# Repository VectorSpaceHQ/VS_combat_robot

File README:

This is an RC controller designed for use in combat robotics. It includes PCB designs for the transmitter and receiver, as well as the necessary Arduino code. It's inspired by the work of Team Panic (https://www.instructables.com/id/Cheap-Arduino-Combat-Robot-Control/), and developed after building and using 12 of their PCBs.

Below are the changes
* Added on/off switch
* Two joysticks, as one is difficult to mix and control. They're also extremely cheap.
* Joysticks connect to female headers rather than being soldered directly. Easily replacable and easier to install.
* Uses a 3.3V Arduino Pro Mini instead of 5V
* Voltage regulator goes directly to VCC and VCC ties to NRF24. This allows powering both components through the USB programmer, no longer requiring a battery to be plugged in for testing.
* Added an LED for active communications indication
* Weapon is now an on/off switch

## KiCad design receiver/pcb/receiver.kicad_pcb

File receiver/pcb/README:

ESP32C3 pin limitations:
https://wiki.seeedstudio.com/exp32c3_d9_d6_d8/

Use D9 only as input. This is the boot button.
Use D6 only as output but it will sometimes be HIGH, so don't use it for any motors!

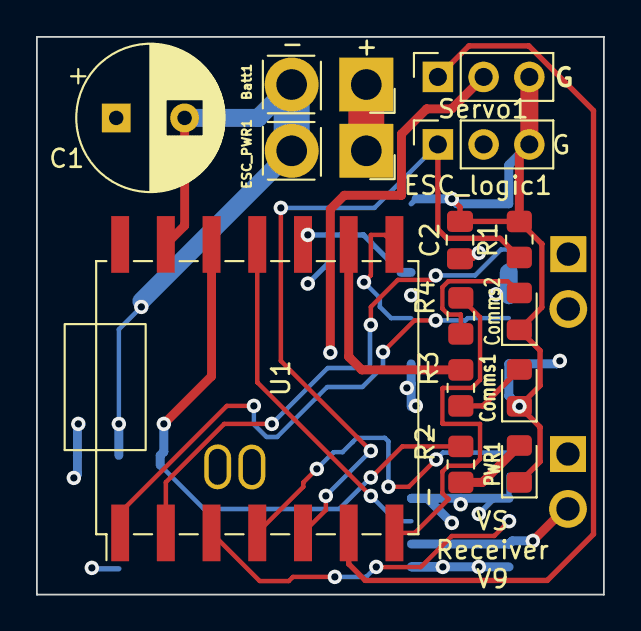
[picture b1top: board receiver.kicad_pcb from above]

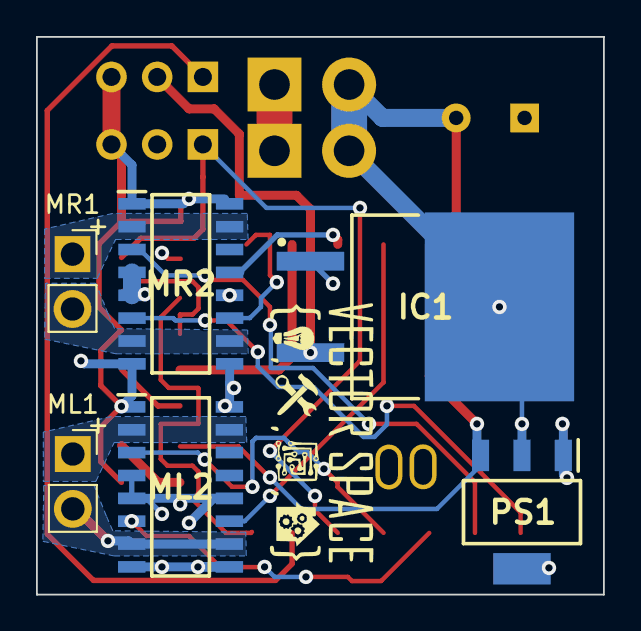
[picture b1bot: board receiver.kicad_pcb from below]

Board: 4 copper layers, 31.5 x 31.0 mm, 20 parts (6 on the bottom side), 22 nets.

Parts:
Batt1: Conn_01x02_Female; battery_pads
C1: 270 uF; CP_Radial_D8.0mm_P3.80mm
C2: 100nF; C_0805_2012Metric_Pad1.18x1.45mm_HandSolder
Comms1, Comms2: LED; LED_0805_2012Metric_Pad1.15x1.40mm_HandSolder
ESC_PWR1: Conn_01x02_Female; battery_pads
ESC_logic1: ESC; PinSocket_1x03_P2.54mm_Vertical
IC1: L7806CD2T-TR; TO254P1542X460-3N
ML1: Conn_01x02_Female; DC_motor_output
ML2: VNH7100BASTR; SOIC127P600X175-16N
MR1: motor_output; DC_motor_output
MR2: VNH7100BASTR; SOIC127P600X175-16N
PS1: UA78M33CDCYRG3; SOT230P700X180-4N
PWR1: LED; LED_0805_2012Metric_Pad1.15x1.40mm_HandSolder
R1: 10k; R_0805_2012Metric_Pad1.20x1.40mm_HandSolder
R2, R3, R4: 680 ohm; R_0805_2012Metric_Pad1.20x1.40mm_HandSolder
Servo1: Servo; PinSocket_1x03_P2.54mm_Vertical
U1: XIAO ESP32C3; xiao_esp32c3

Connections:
+3V3: PS1.3 (OUTPUT), R2.1, U1.12 (VCC_3V3)
+6V: IC1.3 (OUTPUT), Servo1.2
+12V: Batt1.1, C1.1, C2.1, ESC_PWR1.1, IC1.1 (INPUT), ML2.4 (VCC_1), ML2.5 (VCC_2), ML2.12 (VCC_3), MR2.4 (VCC_1), MR2.5 (VCC_2), MR2.12 (VCC_3), PS1.1 (INPUT)
/ML_PWM: ML2.11 (PWM), U1.11 (D10)
/MR_PWM: MR2.11 (PWM), U1.8 (D7)
/MR_sense: MR2.13 (CS), U1.10 (D9)
GND: Batt1.2, C1.2, C2.2, Comms1.1 (K), Comms2.1 (K), ESC_PWR1.2, ESC_logic1.3, IC1.4 (GND_(THERMALPAD)), ML2.1 (GNDA_1), ML2.8 (GNDB_1), ML2.9 (GNDB_2), ML2.16 (GNDA_2), MR2.1 (GNDA_1), MR2.8 (GNDB_1), MR2.9 (GNDB_2), MR2.16 (GNDA_2), PS1.2 (COMMON_1), PS1.4 (COMMON_2), PWR1.1 (K), R1.1, Servo1.3, U1.13 (GND)
unnamed: Comms1.2 (A), R3.2
unnamed: Comms2.2 (A), R4.2
unnamed: ESC_logic1.1, R1.2, U1.5 (D4)
unnamed: ML1.1, ML2.2 (OUTA_1), ML2.15 (OUTA_2)
unnamed: ML1.2, ML2.7 (OUTB_1), ML2.10 (OUTB_2)
unnamed: ML2.3 (INA), U1.4 (D3)
unnamed: ML2.6 (INB), U1.3 (D2)
unnamed: MR1.1, MR2.2 (OUTA_1), MR2.15 (OUTA_2)
unnamed: MR1.2, MR2.7 (OUTB_1), MR2.10 (OUTB_2)
unnamed: MR2.3 (INA), U1.2 (D1)
unnamed: MR2.6 (INB), U1.1 (D0)
unnamed: PWR1.2 (A), R2.2
unnamed: Servo1.1, U1.6 (D5)
unnamed: R4.1, U1.7 (D6)
unnamed: R3.1, U1.9 (D8)

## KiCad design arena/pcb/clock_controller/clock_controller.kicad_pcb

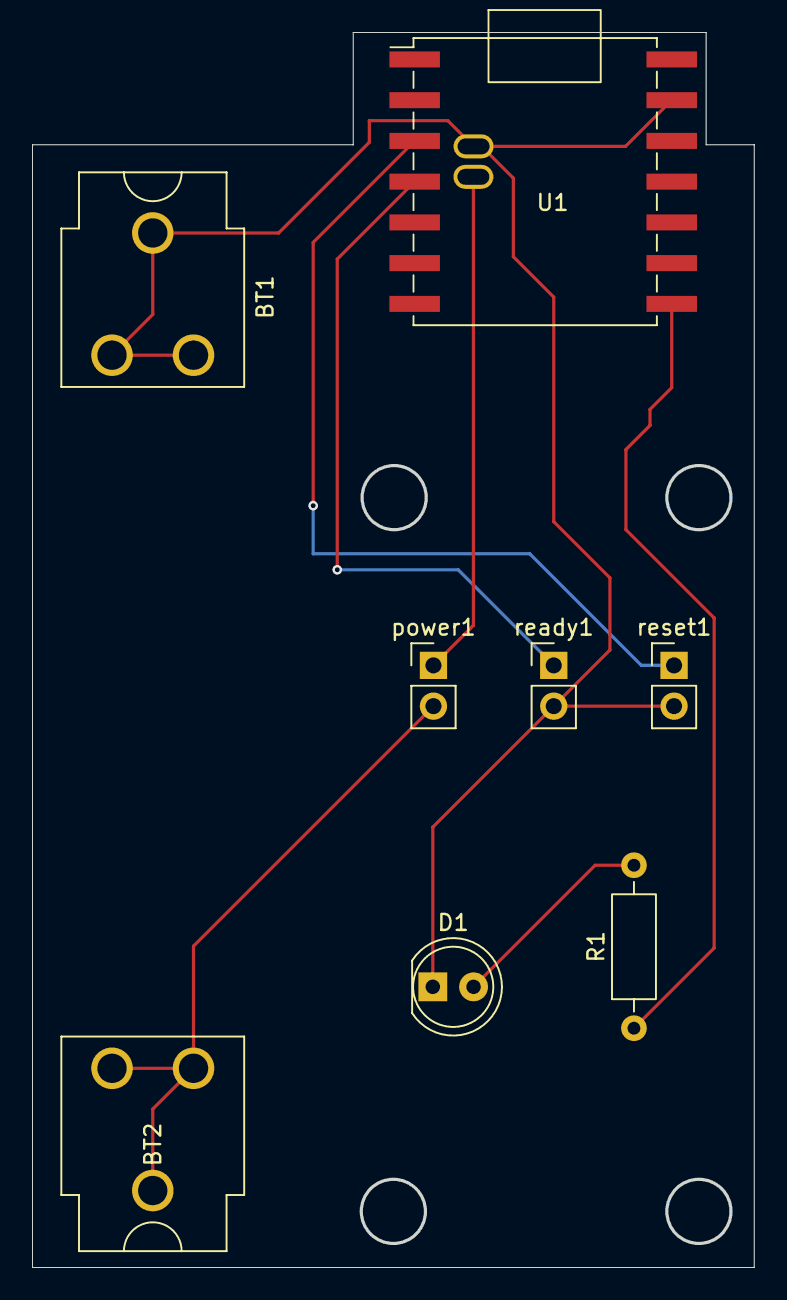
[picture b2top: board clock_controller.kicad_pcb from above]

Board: 2 copper layers, 44.9 x 76.9 mm, 8 parts (0 on the bottom side), 7 nets.

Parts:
BT1, BT2: 54; BatteryClip_Keystone_54_D16-19mm
D1: LED; LED_D5.0mm_FlatTop
R1: R_US; R_Axial_DIN0207_L6.3mm_D2.5mm_P10.16mm_Horizontal
U1: XIAO ESP32C3; xiao_esp32c3
power1: SW_SPDT; PinHeader_1x02_P2.54mm_Vertical
ready1: SW_Push; PinHeader_1x02_P2.54mm_Vertical
reset1: SW_Push; PinHeader_1x02_P2.54mm_Vertical

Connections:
+3.3V: U1.B+ (Batt+), power1.1 (A)
GND: BT1.1, D1.1 (K), U1.13 (GND), U1.B- (Batt-), ready1.2, reset1.2
unnamed: BT2.1 (A), power1.2 (B)
unnamed: D1.2 (A), R1.2
unnamed: U1.3 (D2), reset1.1
unnamed: U1.4 (D3), ready1.1
unnamed: R1.1, U1.8 (D7)

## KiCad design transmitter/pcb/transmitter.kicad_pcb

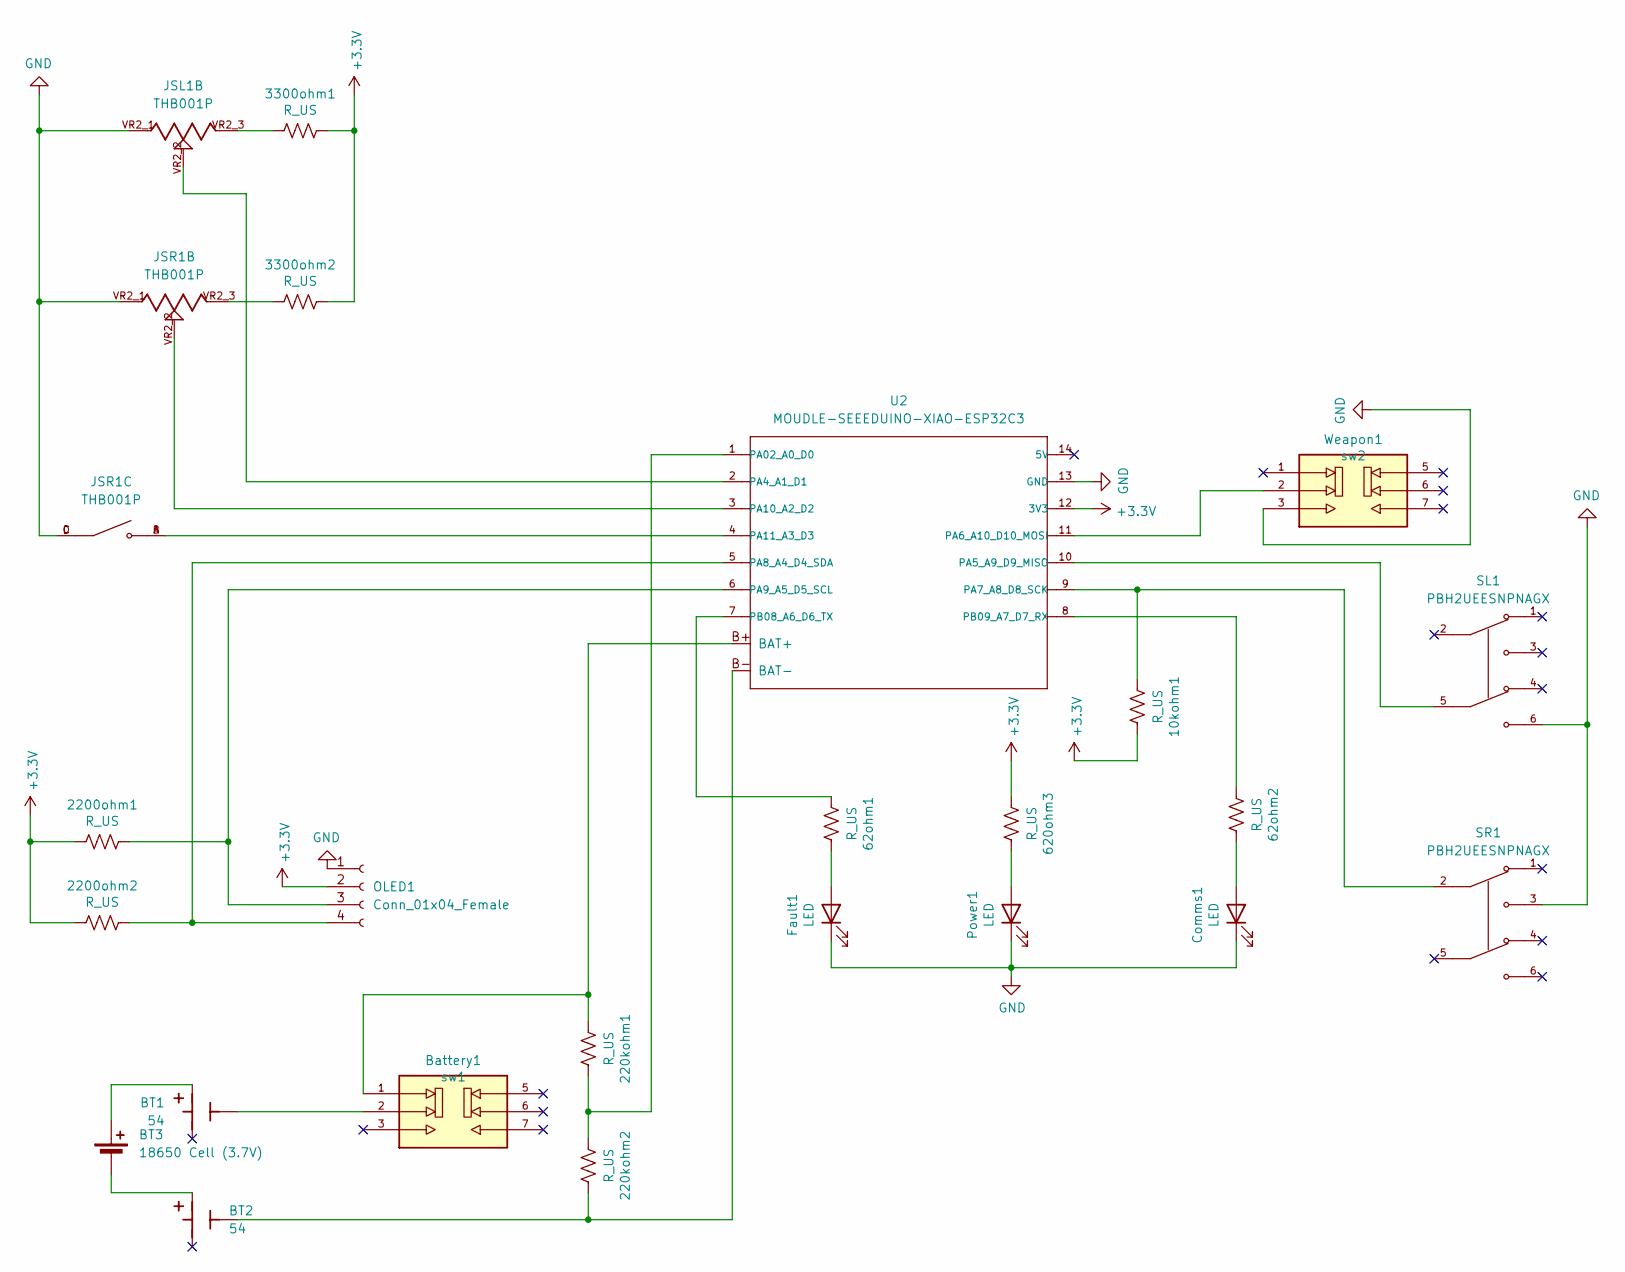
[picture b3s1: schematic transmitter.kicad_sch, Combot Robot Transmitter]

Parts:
10kohm1, 62ohm1, 62ohm2, 220kohm1, 220kohm2, 620ohm3, 2200ohm1, 2200ohm2, 3300ohm1, 3300ohm2: R_US; R_0805_2012Metric_Pad1.20x1.40mm_HandSolder
BT1, BT2: 54; BAT_54; PARTREV E
BT3: 18650 Cell (3.7V)
Battery1: sw1; SW_JS202011JCQN; PARTREV 11 Nov 19
Comms1: LED; LED_0805_2012Metric_Pad1.15x1.40mm_HandSolder
Fault1: LED; LED_0805_2012Metric_Pad1.15x1.40mm_HandSolder
JSL1: THB001P; CNK_THB001P; PARTREV 27 Jan 22
JSR1: THB001P; CNK_THB001P; PARTREV 27 Jan 22
OLED1: Conn_01x04_Female; PinSocket_1x04_P2.54mm_Vertical
Power1: LED; LED_0805_2012Metric_Pad1.15x1.40mm_HandSolder
SL1: PBH2UEESNPNAGX; SW_PBH2UEESNPNAGX; PARTREV E
SR1: PBH2UEESNPNAGX; SW_PBH2UEESNPNAGX; PARTREV E
U2: MOUDLE-SEEEDUINO-XIAO-ESP32C3; MOUDLE14P-SMD-2.54-21X17.8MM
Weapon1: sw2; SW_JS202011JCQN; PARTREV 11 Nov 19

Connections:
+3.3V: 10kohm1.1, 620ohm3.2, 2200ohm1.2, 2200ohm2.2, 3300ohm1.1, 3300ohm2.1, OLED1.2, U2.12 (3V3)
GND: Comms1.1 (K), Fault1.1 (K), JSL1.VR2_1, JSR1.C, JSR1.D, JSR1.VR2_1, OLED1.1, Power1.1 (K), SL1.6, SR1.3, U2.13 (GND), Weapon1.3
unnamed: 3300ohm1.2, JSL1.VR2_3
unnamed: 3300ohm2.2, JSR1.VR2_3
unnamed: BT1.1_3, Battery1.2
unnamed: BT1.1_1, BT3.1 (+)
unnamed: BT2.1_1, BT3.2 (-)
unnamed: 62ohm2.1, Comms1.2 (A)
unnamed: 62ohm1.1, Fault1.2 (A)
unnamed: 2200ohm1.1, OLED1.3, U2.6 (PA9_A5_D5_SCL)
unnamed: 2200ohm2.1, OLED1.4, U2.5 (PA8_A4_D4_SDA)
unnamed: 620ohm3.1, Power1.2 (A)
unnamed: 220kohm1.2, Battery1.1, U2.B+ (BAT+)
unnamed: 220kohm2.1, BT2.1_3, U2.B- (BAT-)
unnamed: 220kohm1.1, 220kohm2.2, U2.1 (PA02_A0_D0)
unnamed: JSL1.VR2_2, U2.2 (PA4_A1_D1)
unnamed: SL1.5, U2.10 (PA5_A9_D9_MISO)
unnamed: U2.11 (PA6_A10_D10_MOSI), Weapon1.2
unnamed: 10kohm1.2, SR1.2, U2.9 (PA7_A8_D8_SCK)
unnamed: JSR1.VR2_2, U2.3 (PA10_A2_D2)
unnamed: JSR1.A, JSR1.B, U2.4 (PA11_A3_D3)
unnamed: 62ohm1.2, U2.7 (PB08_A6_D6_TX)
unnamed: 62ohm2.2, U2.8 (PB09_A7_D7_RX)

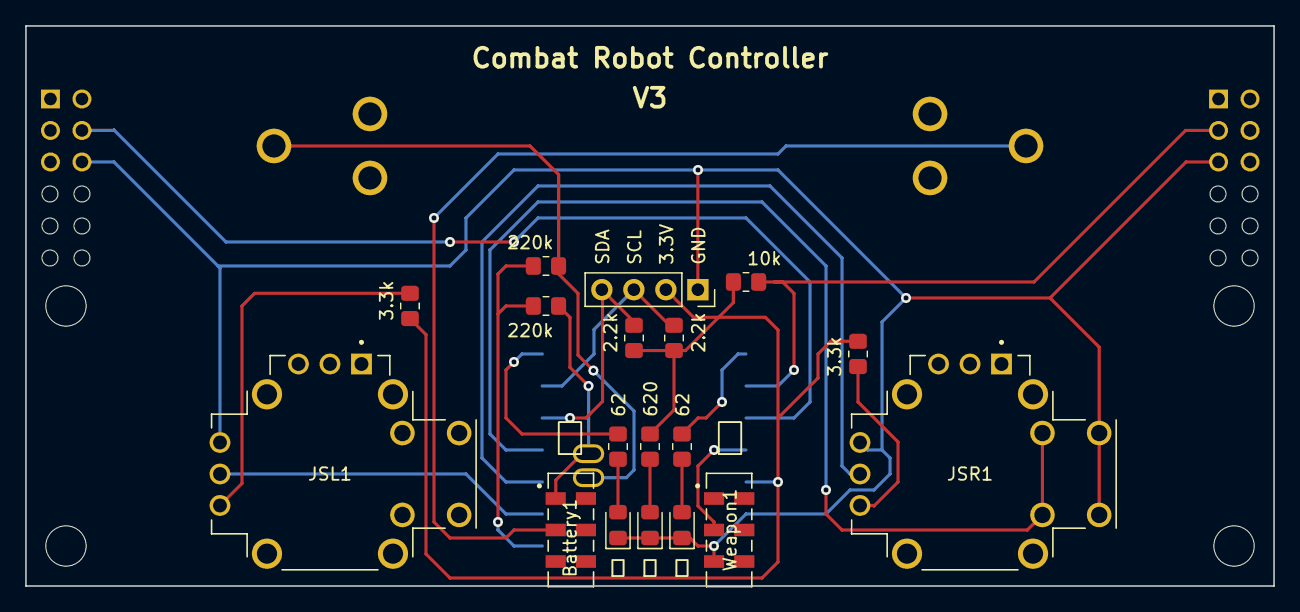
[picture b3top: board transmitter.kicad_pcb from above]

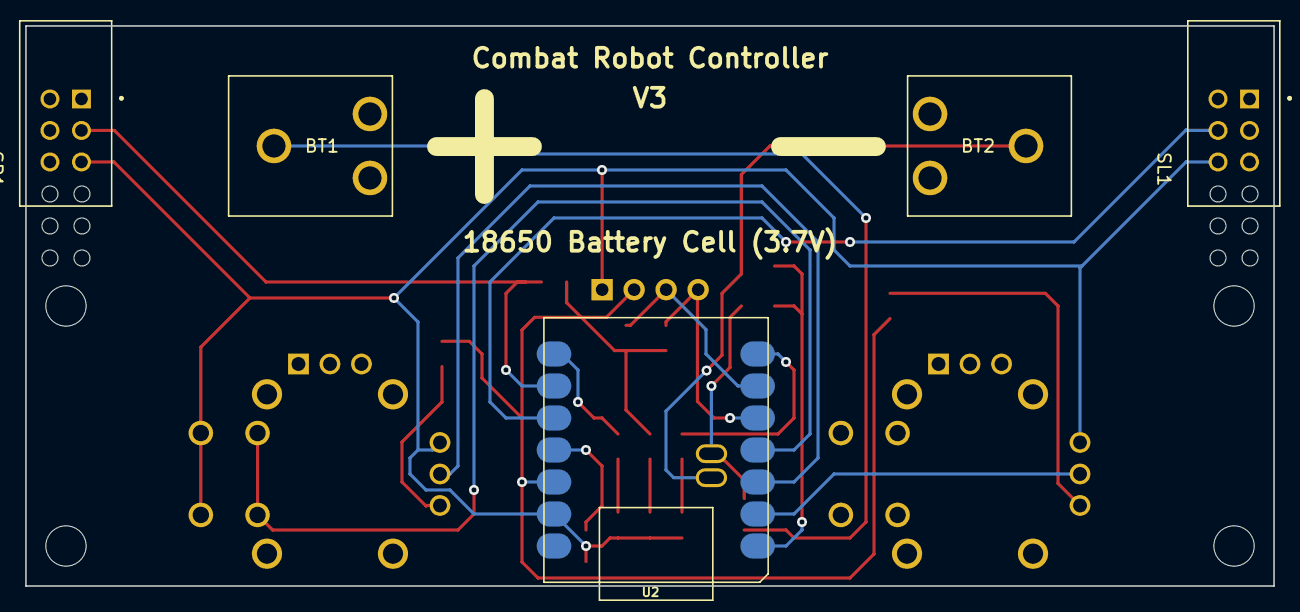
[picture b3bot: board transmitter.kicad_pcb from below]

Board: 2 copper layers, 99.1 x 44.5 mm, 23 parts (5 on the bottom side), 21 nets.

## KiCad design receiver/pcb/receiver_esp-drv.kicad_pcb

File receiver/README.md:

# Hardware
MCU: ESP32-C3
max supply voltage 3.7V

Voltage Regulator: AMS1117-3.3
Max supply voltage 15V. Regulates to 3.3V

Motor Drivers: VNH7100BASTR
Vin: 5V to 28V
15A max

# Software
## Receiver

### Compiling
1. Ensure PlatformIO Core installed
2. Click PlatformIO extension on sidebar
3. Open ./src/receiver as project.
4. Click Upload -> arrow at bottom bar.

## Transmitter
### Installation
#### Determine MAC Address of ESP32
1. Upload MAC_finder.ino using Arduino IDE
2. Look at Serial Monitor and copy down resulting MAC address
3. Copy this MAC Address into transmitter.ino

OR

Arduino IDE -> Tools -> Get Board Info

#### Determine joystick rest values

# Troubleshooting
## ESP32 Error: No serial data received

1. Open the Arduino IDE Serial Monitor
2. Hold-down the “BOOT” button
3. Press the “ENABLE” button once
4. Release the finger from the “BOOT” button

## ESP32 Error: A serial exception error occurred: Write timeout
 Press and hold the R button, then press and hold the B button, then release the R button, then release the B button.

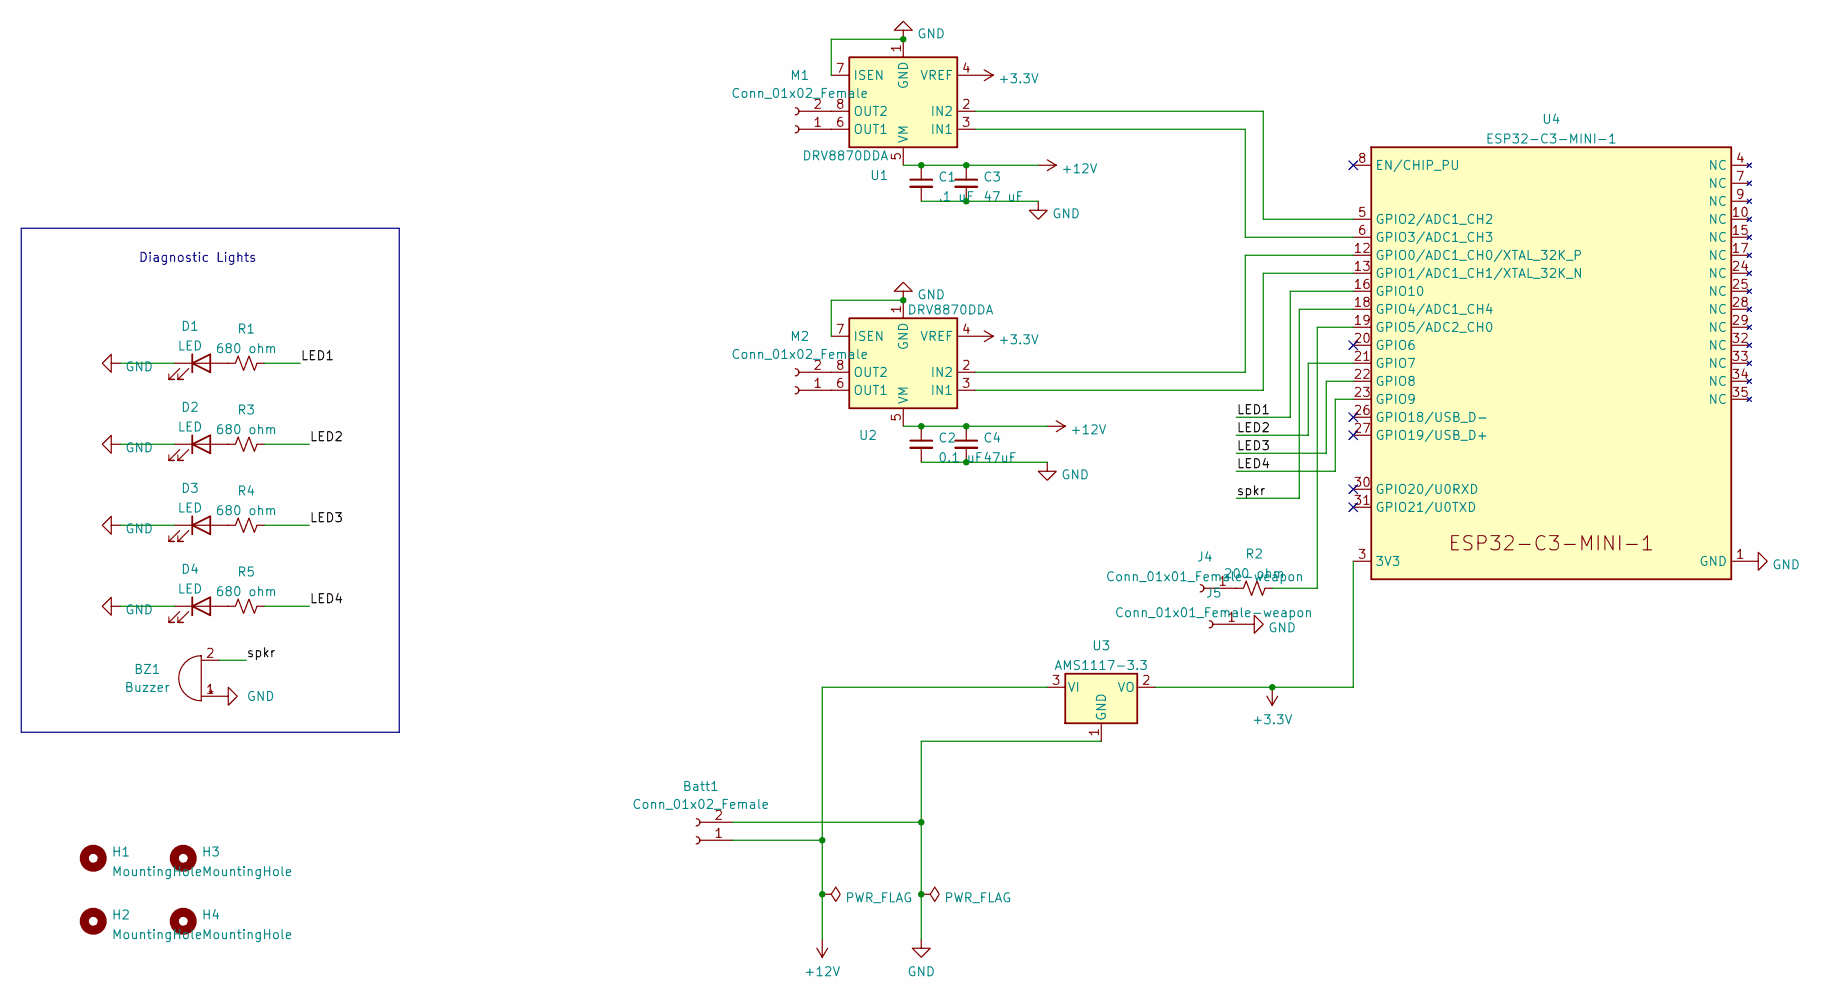
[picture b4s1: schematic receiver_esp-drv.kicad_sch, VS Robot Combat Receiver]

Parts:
BZ1: Buzzer; Buzzer_CUI_CPT-9019S-SMT
Batt1: Conn_01x02_Female; PinSocket_1x02_P2.54mm_Vertical
C1: .1 uF; C_0805_2012Metric_Pad1.18x1.45mm_HandSolder
C2: 0.1 uF; C_0805_2012Metric_Pad1.18x1.45mm_HandSolder
C3: 47 uF; C_0805_2012Metric_Pad1.18x1.45mm_HandSolder
C4: 47uF; C_0805_2012Metric_Pad1.18x1.45mm_HandSolder
D1, D2, D3, D4: LED; LED_0805_2012Metric_Pad1.15x1.40mm_HandSolder
H1, H2, H3, H4: MountingHole; MountingHole_3.2mm_M3
J4, J5: Conn_01x01_Female-weapon; PinSocket_1x01_P2.54mm_Vertical
M1, M2: Conn_01x02_Female; PinSocket_1x02_P2.54mm_Vertical
R1, R3, R4, R5: 680 ohm; R_0805_2012Metric_Pad1.20x1.40mm_HandSolder
R2: 200 ohm; R_0805_2012Metric_Pad1.20x1.40mm_HandSolder
U1, U2: DRV8870DDA; Texas_HTSOP-8-1EP_3.9x4.9mm_P1.27mm_EP2.95x4.9mm_Mask2.4x3.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
U3: AMS1117-3.3; SOT-223-3_TabPin2
U4: ESP32-C3-MINI-1; ESP32-C3

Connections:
+3V3: U1.4 (VREF), U2.4 (VREF), U3.2 (VO), U4.3 (3V3)
+12V: Batt1.1, C1.1, C2.1, C3.1, C4.1, U1.5 (VM), U2.5 (VM), U3.3 (VI)
/LED1: R1.1, U4.16 (GPIO10)
/LED2: R3.1, U4.21 (GPIO7)
/LED3: R4.1, U4.22 (GPIO8)
/LED4: R5.1, U4.23 (GPIO9)
/spkr: BZ1.2 (+), U4.18 (GPIO4/ADC1_CH4)
GND: BZ1.1 (-), Batt1.2, C1.2, C2.2, C3.2, C4.2, D1.1 (K), D2.1 (K), D3.1 (K), D4.1 (K), J5.1, U1.1 (GND), U1.7 (ISEN), U1.9 (GND), U2.1 (GND), U2.7 (ISEN), U2.9 (GND), U3.1 (GND), U4.1 (GND), U4.2 (GND), U4.36 (GND), U4.37 (GND), U4.38 (GND), U4.39 (GND), U4.40 (GND), U4.41 (GND), U4.42 (GND), U4.43 (GND), U4.44 (GND), U4.45 (GND), U4.46 (GND), U4.47 (GND), U4.48 (GND), U4.49 (GND), U4.50 (GND), U4.51 (GND), U4.52 (GND), U4.53 (GND)
unnamed: D1.2 (A), R1.2
unnamed: D2.2 (A), R3.2
unnamed: D3.2 (A), R4.2
unnamed: D4.2 (A), R5.2
unnamed: J4.1, R2.2
unnamed: M1.1, U1.6 (OUT1)
unnamed: M1.2, U1.8 (OUT2)
unnamed: M2.1, U2.6 (OUT1)
unnamed: M2.2, U2.8 (OUT2)
unnamed: R2.1, U4.19 (GPIO5/ADC2_CH0)
unnamed: U1.2 (IN2), U4.5 (GPIO2/ADC1_CH2)
unnamed: U1.3 (IN1), U4.6 (GPIO3/ADC1_CH3)
unnamed: U2.2 (IN2), U4.12 (GPIO0/ADC1_CH0/XTAL_32K_P)
unnamed: U2.3 (IN1), U4.13 (GPIO1/ADC1_CH1/XTAL_32K_N)

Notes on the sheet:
Diagnostic Lights

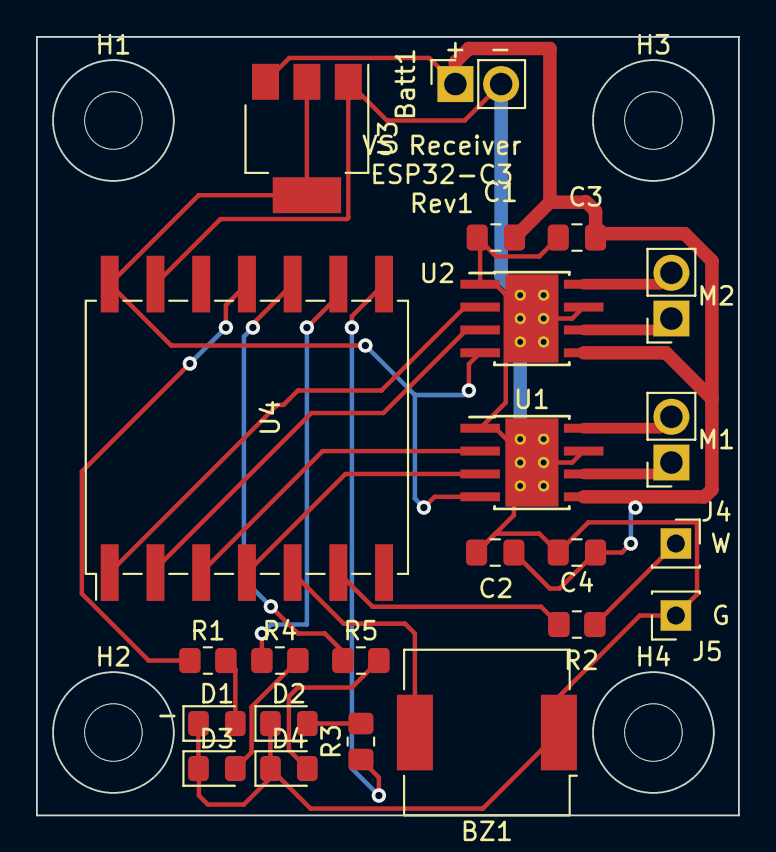
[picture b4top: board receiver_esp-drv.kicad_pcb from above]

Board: 2 copper layers, 39.0 x 43.2 mm, 27 parts (0 on the bottom side), 22 nets.

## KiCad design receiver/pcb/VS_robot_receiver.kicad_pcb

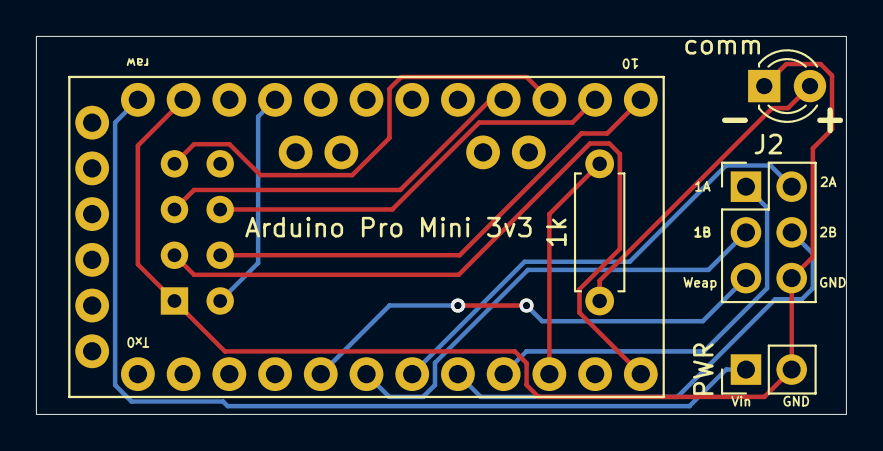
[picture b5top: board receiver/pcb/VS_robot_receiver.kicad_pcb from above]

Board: 2 copper layers, 45.0 x 21.0 mm, 6 parts (1 on the bottom side), 16 nets.

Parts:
1k: 680ohm; R_Axial_DIN0207_L6.3mm_D2.5mm_P7.62mm_Horizontal
Arduino Pro Mini 3v3: ARDUINO_PRO_MINI; MODULE_ARDUINO_PRO_MINI
J2: Conn_02x03_Odd_Even; PinHeader_2x03_P2.54mm_Vertical
NRF24: NRF24L01_Breakout; nRF24L01_Breakout
PWR: Conn_01x02_Female; PinHeader_1x02_P2.54mm_Vertical
comm: LED; LED_D3.0mm

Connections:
+3V3: Arduino Pro Mini 3v3.JP6_4, NRF24.2
+5V: Arduino Pro Mini 3v3.JP6_1, PWR.1
GND: Arduino Pro Mini 3v3.JP6_2, J2.6, NRF24.1, PWR.2, comm.1
unnamed: 1k.1, comm.2
unnamed: Arduino Pro Mini 3v3.JP7_4, J2.1
unnamed: Arduino Pro Mini 3v3.JP7_6, J2.2
unnamed: Arduino Pro Mini 3v3.JP7_7, J2.3
unnamed: Arduino Pro Mini 3v3.JP7_5, J2.4
unnamed: Arduino Pro Mini 3v3.JP7_8, J2.5
unnamed: 1k.2, Arduino Pro Mini 3v3.JP7_3
unnamed: Arduino Pro Mini 3v3.JP7_1, NRF24.3
unnamed: Arduino Pro Mini 3v3.JP6_12, NRF24.4
unnamed: Arduino Pro Mini 3v3.JP6_9, NRF24.5
unnamed: Arduino Pro Mini 3v3.JP6_11, NRF24.6
unnamed: Arduino Pro Mini 3v3.JP6_10, NRF24.7
unnamed: Arduino Pro Mini 3v3.JP1_5, Arduino Pro Mini 3v3.JP1_6

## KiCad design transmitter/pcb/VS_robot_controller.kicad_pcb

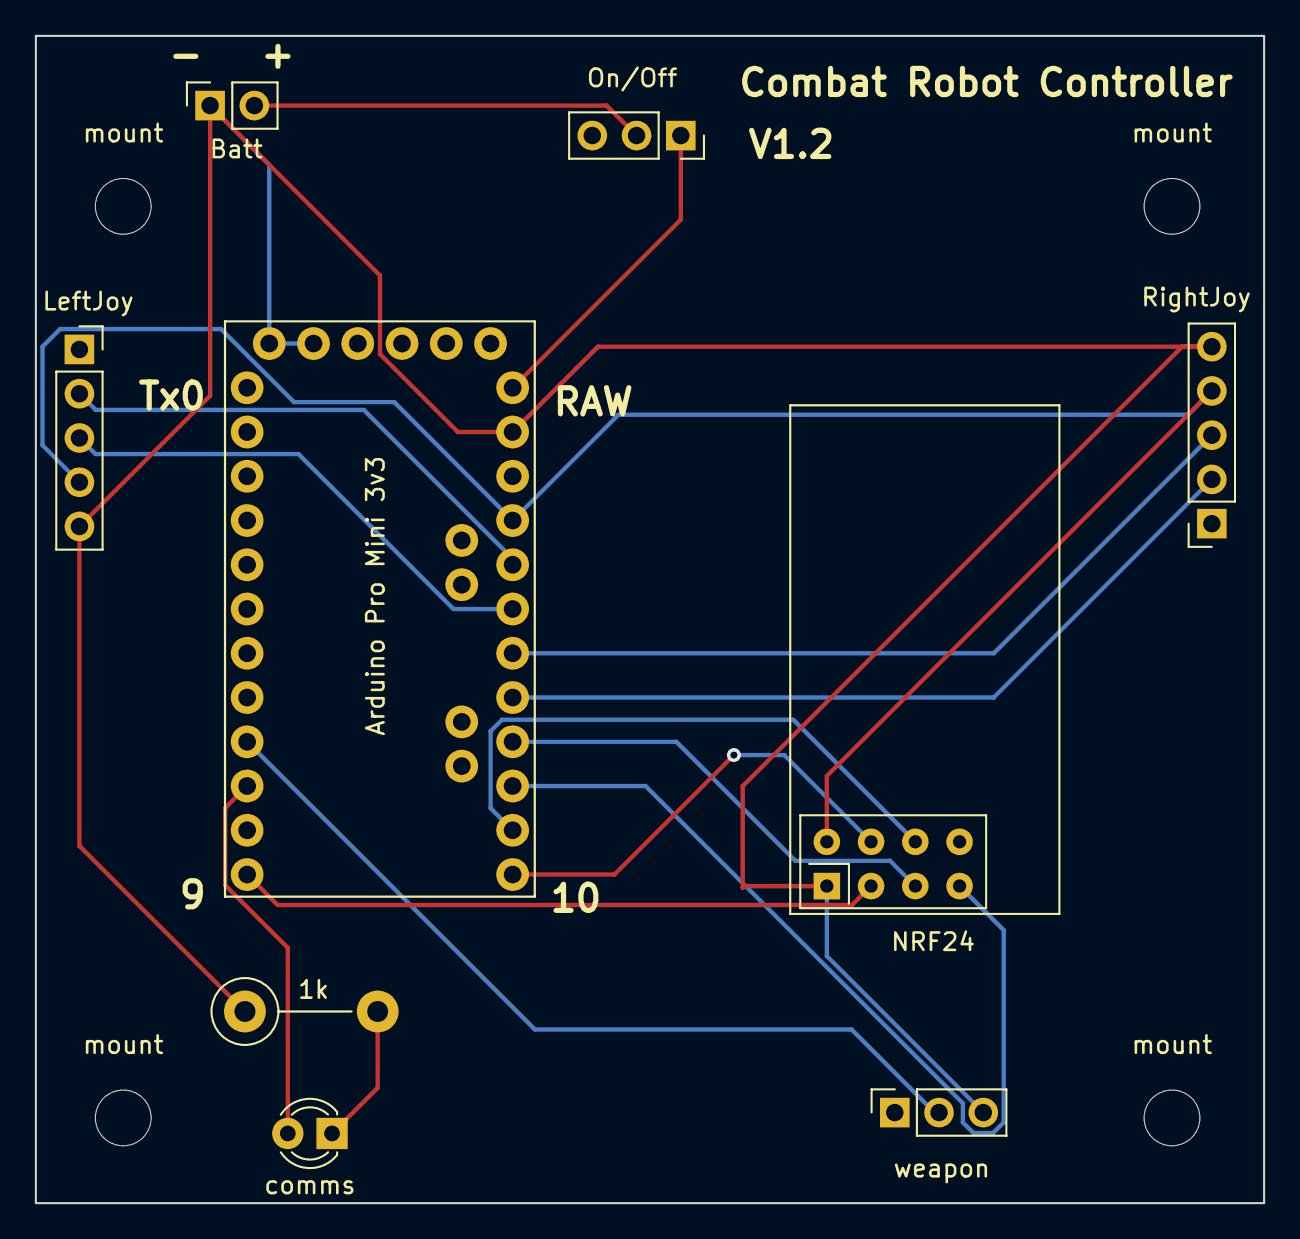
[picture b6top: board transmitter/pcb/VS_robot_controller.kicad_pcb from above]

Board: 2 copper layers, 70.5 x 67.0 mm, 13 parts (0 on the bottom side), 16 nets.

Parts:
1k: R_US; R_Axial_DIN0411_L9.9mm_D3.6mm_P7.62mm_Vertical
Arduino Pro Mini 3v3: ARDUINO_PRO_MINI; MODULE_ARDUINO_PRO_MINI
Batt: j2; PinSocket_1x02_P2.54mm_Vertical
LeftJoy: J3; PinSocket_1x05_P2.54mm_Vertical
NRF24: NRF24L01_Breakout; nRF24L01_Breakout
On/Off: sw1; PinSocket_1x03_P2.54mm_Vertical
RightJoy: J4; PinSocket_1x05_P2.54mm_Vertical
comms: LED; LED_D3.0mm
mount: MountingHole_3.2mm_M3
mount#2, mount#3, mount#4: MountingHole_3.2mm_M3
weapon: sw2; PinSocket_1x03_P2.54mm_Vertical

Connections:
+3V3: Arduino Pro Mini 3v3.JP6_4, LeftJoy.4, NRF24.2, RightJoy.4
+9V: Batt.2, On/Off.2
GND: 1k.1, Arduino Pro Mini 3v3.JP1_5, Arduino Pro Mini 3v3.JP1_6, Arduino Pro Mini 3v3.JP6_2, Batt.1, LeftJoy.5, NRF24.1, RightJoy.5, weapon.3
unnamed: 1k.2, comms.1
unnamed: Arduino Pro Mini 3v3.JP6_5, LeftJoy.2
unnamed: Arduino Pro Mini 3v3.JP6_6, LeftJoy.3
unnamed: Arduino Pro Mini 3v3.JP6_1, On/Off.1
unnamed: Arduino Pro Mini 3v3.JP6_8, RightJoy.2
unnamed: Arduino Pro Mini 3v3.JP6_7, RightJoy.3
unnamed: Arduino Pro Mini 3v3.JP7_1, NRF24.3
unnamed: Arduino Pro Mini 3v3.JP6_12, NRF24.4
unnamed: Arduino Pro Mini 3v3.JP6_9, NRF24.5
unnamed: Arduino Pro Mini 3v3.JP6_11, NRF24.6
unnamed: Arduino Pro Mini 3v3.JP6_10, NRF24.7
unnamed: Arduino Pro Mini 3v3.JP7_3, comms.2
unnamed: Arduino Pro Mini 3v3.JP7_4, weapon.2

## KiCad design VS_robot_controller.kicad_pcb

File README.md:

This is an open source, low cost, DIY combat robot kit. It is designed for use with antweight (1lb) and beetleweight (3lb) combat robots.

This repository includes PCB designs for the transmitter and receiver, the associated software, as well as a simple 3d printable chassis and controller design.

# Pairing Receiver and Transmitter
- On the receiver, hold the B button for 3 seconds to enter pairing mode.
- On the transmitter, hold L trigger, R trigger, and depress the right thumb joystick at the same time for 3 seconds to enter pairing mode. Once in pairing mode, the wifi LED will blink rapidly. The transmitter will stay in this state for 15 seconds unless it is paired quicker.
- Once paired, the comms1 LED on the receiver will blink slowly, like a heartbeat. The transmitter LCD will show Robot Connected.

# Troubleshooting

# Invalid head of packet
If the following error occurs when trying to upload to the ESP32, the fix is to hold pin D9 to ground while powering on the board.

A fatal error occurred: Invalid head of packet (0x01): Possible serial noise or corruption.
Failed uploading: uploading error: exit status 2

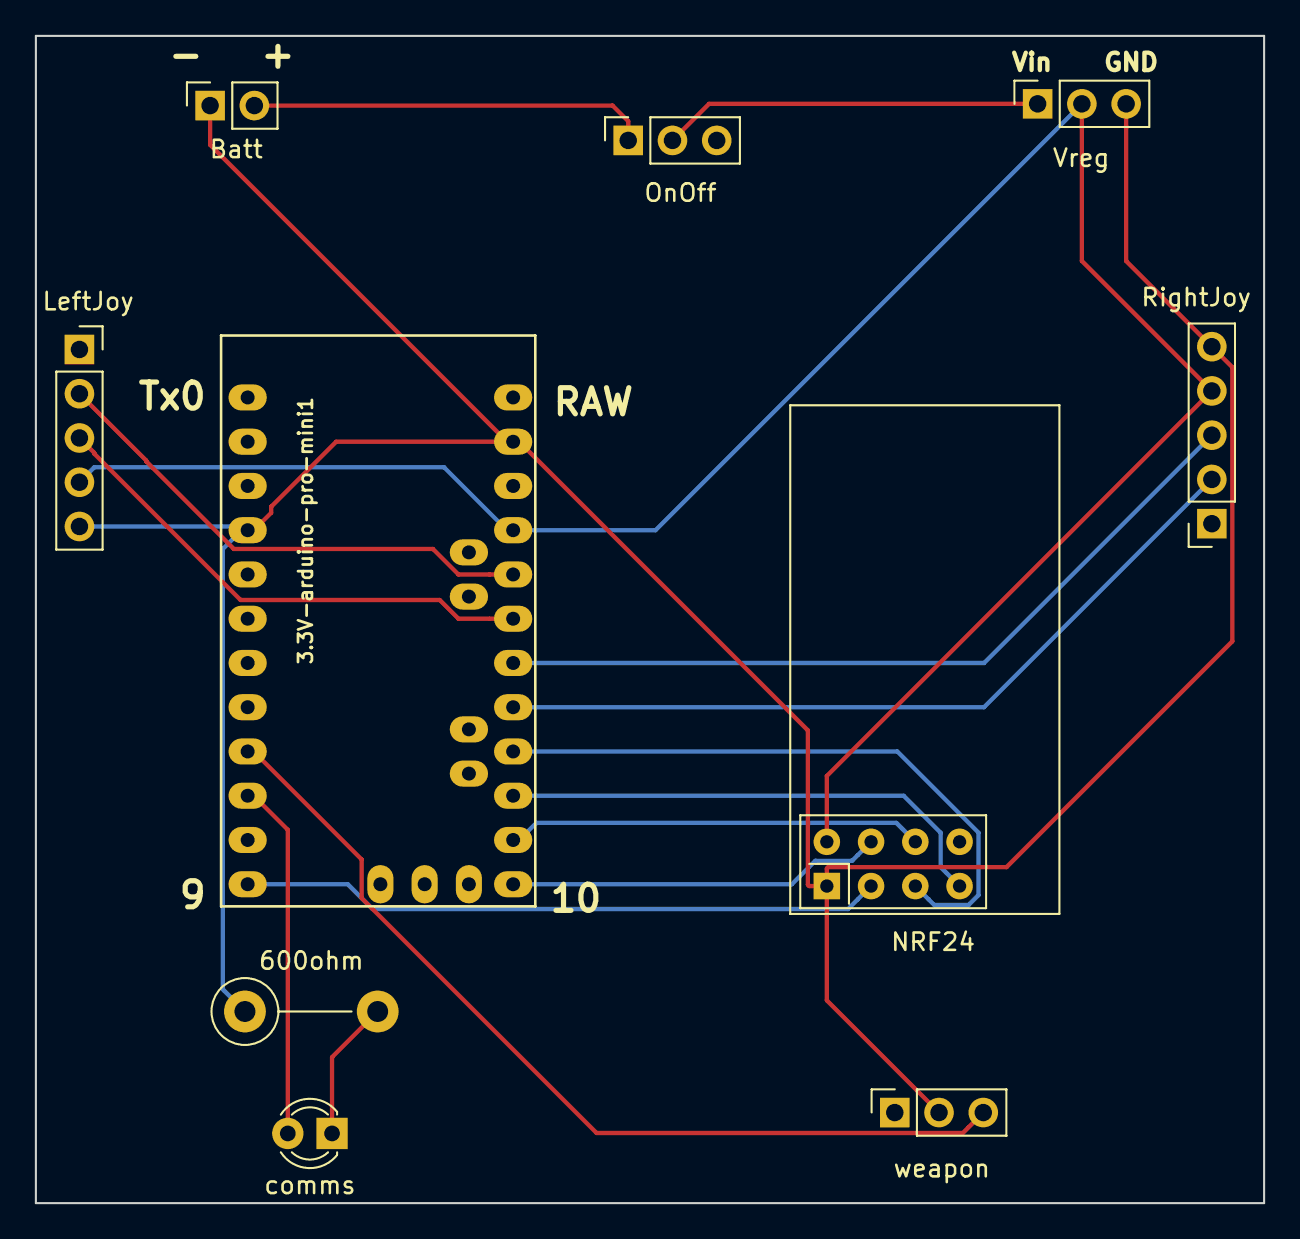
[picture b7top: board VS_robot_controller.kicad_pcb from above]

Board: 2 copper layers, 70.5 x 67.0 mm, 10 parts (0 on the bottom side), 15 nets.

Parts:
3.3V-arduino-pro-mini1: arduino-pro-mini; pro_mini
600ohm: R_US; R_Axial_DIN0411_L9.9mm_D3.6mm_P7.62mm_Vertical
Batt: j2; PinSocket_1x02_P2.54mm_Vertical
LeftJoy: J3; PinSocket_1x05_P2.54mm_Vertical
NRF24: NRF24L01_Breakout; nRF24L01_Breakout
OnOff: sw1; PinSocket_1x03_P2.54mm_Vertical
RightJoy: J4; PinSocket_1x05_P2.54mm_Vertical
Vreg: j3; PinSocket_1x03_P2.54mm_Vertical
comms: LED; LED_D3.0mm
weapon: sw2; PinSocket_1x03_P2.54mm_Vertical

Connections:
+3V3: 3.3V-arduino-pro-mini1.21, LeftJoy.4, NRF24.2, RightJoy.4, Vreg.2
+12V: Batt.2, OnOff.1, OnOff.2, Vreg.1
GND: 3.3V-arduino-pro-mini1.4, 3.3V-arduino-pro-mini1.23, 600ohm.1, Batt.1, LeftJoy.5, NRF24.1, RightJoy.5, Vreg.3, weapon.2
unnamed: 3.3V-arduino-pro-mini1.9, weapon.3
unnamed: 3.3V-arduino-pro-mini1.10, comms.2
unnamed: 3.3V-arduino-pro-mini1.12, NRF24.3
unnamed: 3.3V-arduino-pro-mini1.13, NRF24.4
unnamed: 3.3V-arduino-pro-mini1.14, NRF24.6
unnamed: 3.3V-arduino-pro-mini1.15, NRF24.7
unnamed: 3.3V-arduino-pro-mini1.16, NRF24.5
unnamed: 3.3V-arduino-pro-mini1.17, RightJoy.2
unnamed: 3.3V-arduino-pro-mini1.18, RightJoy.3
unnamed: 3.3V-arduino-pro-mini1.19, LeftJoy.3
unnamed: 3.3V-arduino-pro-mini1.20, LeftJoy.2
unnamed: 600ohm.2, comms.1

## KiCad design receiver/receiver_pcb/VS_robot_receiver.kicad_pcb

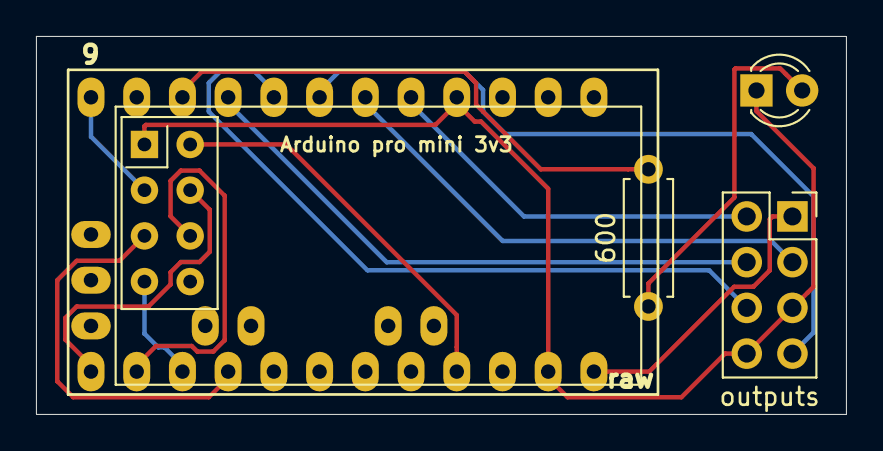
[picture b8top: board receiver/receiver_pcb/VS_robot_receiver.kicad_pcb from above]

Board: 2 copper layers, 45.0 x 21.0 mm, 5 parts (0 on the bottom side), 15 nets.

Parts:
600: 600; R_Axial_DIN0207_L6.3mm_D2.5mm_P7.62mm_Horizontal
Arduino pro mini 3v3: arduino-pro-mini; pro_mini
D1: comms; LED_D3.0mm
J2: outputs; PinSocket_2x04_P2.54mm_Vertical
NRF24: NRF24L01_Breakout; nRF24L01_Breakout

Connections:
+3V3: Arduino pro mini 3v3.21, NRF24.2
+5V: Arduino pro mini 3v3.24, J2.1
GND: Arduino pro mini 3v3.4, Arduino pro mini 3v3.23, D1.1, J2.5, J2.8, NRF24.1
unnamed: 600.1, D1.2
unnamed: Arduino pro mini 3v3.5, J2.2
unnamed: Arduino pro mini 3v3.6, J2.3
unnamed: Arduino pro mini 3v3.9, J2.4
unnamed: Arduino pro mini 3v3.8, J2.6
unnamed: Arduino pro mini 3v3.7, J2.7
unnamed: 600.2, Arduino pro mini 3v3.10
unnamed: Arduino pro mini 3v3.12, NRF24.3
unnamed: Arduino pro mini 3v3.13, NRF24.4
unnamed: Arduino pro mini 3v3.14, NRF24.6
unnamed: Arduino pro mini 3v3.15, NRF24.7
unnamed: Arduino pro mini 3v3.16, NRF24.5
